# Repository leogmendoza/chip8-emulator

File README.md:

# 🍪 CHIP ATE

## 🤔 What?
CHIP ATE is a CHIP-8 Emulator implemented on both PC using SDL2 and STM32 with a custom PCB!

## 🤨 Why?
This was supposed to be my first step into console emulation, but then it became that for PCB design as well!

## Features
- **Portable Emulator Core**:  
  Implements the timers, memory, and CPU as per the [official CHIP-8 spec](http://devernay.free.fr/hacks/chip8/C8TECH10.HTM), including all 34 instructions

- **Platform Abstraction Layer**:  
  Able to run on either PC or STM32 using a platform-agnostic API layer
  
- **Custom PCB**:  
  Assembled on a STM32-based board with an OLED screen, keypad, a buzzer, and power regulation
  
- **ROM Menu**:  
  Provides seamless loading in and out of the ROM catalog

## Diagrams

### System Architecture

### Schematic

### Routing and 3D Renders

## 📸 STM32 Demos

### Demo Video (click it!)

### Tetris

### Tic-Tac-Toe

### Pong

## 📸 PC Demos

### Demo Video (click it!)

### Startup Screen

### Menu

### Opcode Test

## Resources
- [Guide to Making a CHIP-8 Emulator](https://tobiasvl.github.io/blog/write-a-chip-8-emulator/) by Tobias V. Langhoff
- [Building a CHIP-8 Emulator in C++](https://austinmorlan.com/posts/chip8_emulator/) by Austin Morlan
- [chip8stm32 Repo](https://github.com/AlfonsoJLuna/chip8stm32) by AlfonsoJLuna
- [KiCad Tutorial Playlist](https://youtube.com/playlist?list=PL3bNyZYHcRSUhUXUt51W6nKvxx2ORvUQB&si=zccgU5XXFSJnHfGM) by Shawn Hymel
- [KiCad 7 PCB Layout in 5 Steps](https://youtu.be/3FGNw28xBr0?si=mEvIMN-HYlVow5y7) by The Design Graveyard

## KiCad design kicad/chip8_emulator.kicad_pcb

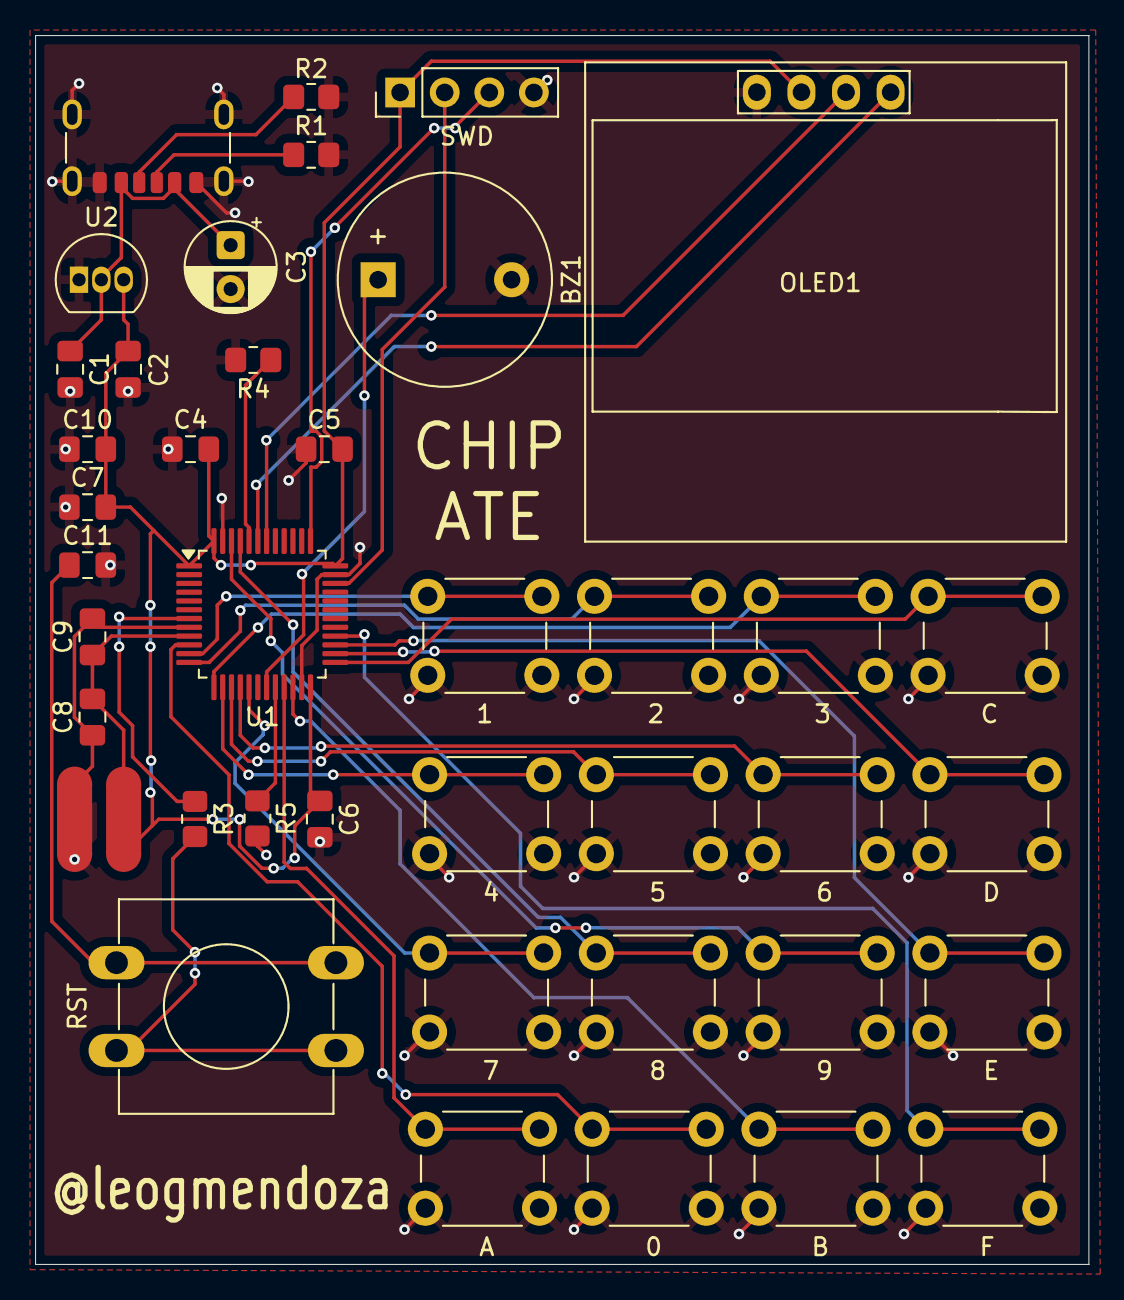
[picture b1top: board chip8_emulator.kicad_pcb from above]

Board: 2 copper layers, 60.0 x 70.0 mm, 41 parts (0 on the bottom side), 33 nets.

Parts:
BZ1: Buzzer; Buzzer_12x9.5RM7.6
C1, C2, C9: 1uF; C_0805_2012Metric_Pad1.18x1.45mm_HandSolder
C3: 10uF; CP_Radial_D5.0mm_P2.50mm
C4, C5, C6, C7, C8, C11: 100nF; C_0805_2012Metric_Pad1.18x1.45mm_HandSolder
C10: 4.7uF; C_0805_2012Metric_Pad1.18x1.45mm_HandSolder
J1: USB-C Power In; USB_C_Receptacle_GCT_USB4125-xx-x_6P_TopMnt_Horizontal
J2: SWD; PinHeader_1x04_P2.54mm_Vertical
NT1, NT2: NetTie_2; NetTie-2_SMD_Pad2.0mm
OLED1: SSD1306; 128x64OLED
R1, R2: 5.1k; R_0805_2012Metric_Pad1.20x1.40mm_HandSolder
R3, R4, R5: 10k; R_0805_2012Metric_Pad1.20x1.40mm_HandSolder
SW1: 1; SW_PUSH_6mm_H4.3mm
SW2: 2; SW_PUSH_6mm_H4.3mm
SW3: 3; SW_PUSH_6mm_H4.3mm
SW4: C; SW_PUSH_6mm_H4.3mm
SW5: 4; SW_PUSH_6mm_H4.3mm
SW6: 5; SW_PUSH_6mm_H4.3mm
SW7: 6; SW_PUSH_6mm_H4.3mm
SW8: D; SW_PUSH_6mm_H4.3mm
SW9: 7; SW_PUSH_6mm_H4.3mm
SW10: 8; SW_PUSH_6mm_H4.3mm
SW11: 9; SW_PUSH_6mm_H4.3mm
SW12: E; SW_PUSH_6mm_H4.3mm
SW13: A; SW_PUSH_6mm_H4.3mm
SW14: 0; SW_PUSH_6mm_H4.3mm
SW15: B; SW_PUSH_6mm_H4.3mm
SW16: F; SW_PUSH_6mm_H4.3mm
SW17: RST; SW_PUSH-12mm
U1: STM32F103C8Tx; LQFP-48_7x7mm_P0.5mm
U2: MCP1700x-330xxTO; TO-92_Inline

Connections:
+3V3: C2.1, C4.2, C5.2, C6.2, C7.2, C10.2, J2.1, NT1.2, OLED1.2 (VCC), U1.1 (VBAT), U1.24 (VDD), U1.36 (VDD), U1.48 (VDD), U2.3 (VO)
+5V: C1.1, C3.1, J1.A9 (VBUS), J1.B9 (VBUS), U2.2 (VI)
/BOOT0: R4.2, U1.44 (BOOT0)
/BOOT1: R5.2, U1.20 (PB2)
/BUZZER: BZ1.1 (+), U1.19 (PB1)
/I2C1_SCL: OLED1.3 (SCL), U1.42 (PB6)
/I2C1_SDA: OLED1.4 (SDA), U1.43 (PB7)
/KEY_0: SW14.1, U1.10 (PA0)
/KEY_1: SW1.1, U1.11 (PA1)
/KEY_2: SW2.1, U1.12 (PA2)
/KEY_3: SW3.1, U1.13 (PA3)
/KEY_4: SW5.1, U1.14 (PA4)
/KEY_5: SW6.1, U1.15 (PA5)
/KEY_6: SW7.1, U1.16 (PA6)
/KEY_7: SW9.1, U1.17 (PA7)
/KEY_8: SW10.1, U1.45 (PB8)
/KEY_9: SW11.1, U1.46 (PB9)
/KEY_A: SW13.1, U1.21 (PB10)
/KEY_B: SW15.1, U1.22 (PB11)
/KEY_C: SW4.1, U1.25 (PB12)
/KEY_D: SW8.1, U1.26 (PB13)
/KEY_E: SW12.1, U1.27 (PB14)
/KEY_F: SW16.1, U1.28 (PB15)
/NRST: R3.1, U1.7 (NRST)
/SWCLK: J2.3, U1.37 (PA14)
/SWDIO: J2.2, U1.34 (PA13)
/VDDA: C8.2, C9.1, NT1.1, U1.9 (VDDA)
/VSSA: C8.1, C9.2, NT2.2, U1.8 (VSSA)
GND: BZ1.2 (-), C1.2, C2.2, C3.2, C4.1, C5.1, C6.1, C7.1, C10.1, C11.1, J1.A12 (GND), J1.B12 (GND), J1.S1 (SHIELD), J2.4, NT2.1, OLED1.1 (GND), R1.2, R2.2, R4.1, R5.1, SW1.2, SW2.2, SW3.2, SW4.2, SW5.2, SW6.2, SW7.2, SW8.2, SW9.2, SW10.2, SW11.2, SW12.2, SW13.2, SW14.2, SW15.2, SW16.2, U1.23 (VSS), U1.35 (VSS), U1.47 (VSS), U2.1 (GND)
unnamed: C11.2, SW17.1
unnamed: J1.A5 (CC1), R1.1
unnamed: J1.B5 (CC2), R2.1
unnamed: R3.2, SW17.2

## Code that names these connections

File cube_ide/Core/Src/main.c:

/* USER CODE BEGIN Header */
/**
  ******************************************************************************
  * @file           : main.c
  * @brief          : Main program body
  ******************************************************************************
  * @attention
  *
  * Copyright (c) 2025 STMicroelectronics.
  * All rights reserved.
  *
  * This software is licensed under terms that can be found in the LICENSE file
  * in the root directory of this software component.
  * If no LICENSE file comes with this software, it is provided AS-IS.
  *
  ******************************************************************************
  */
/* USER CODE END Header */
/* Includes ------------------------------------------------------------------*/
#include "main.h"

/* Private includes ----------------------------------------------------------*/
/* USER CODE BEGIN Includes */
#include "chip8.h"
#include "app.h"
/* USER CODE END Includes */

/* Private typedef -----------------------------------------------------------*/
/* USER CODE BEGIN PTD */

/* USER CODE END PTD */

/* Private define ------------------------------------------------------------*/
/* USER CODE BEGIN PD */

/* USER CODE END PD */

/* Private macro -------------------------------------------------------------*/
/* USER CODE BEGIN PM */

/* USER CODE END PM */

/* Private variables ---------------------------------------------------------*/
I2C_HandleTypeDef hi2c1;

TIM_HandleTypeDef htim3;

/* USER CODE BEGIN PV */

/* USER CODE END PV */

/* Private function prototypes -----------------------------------------------*/
void SystemClock_Config(void);
static void MX_GPIO_Init(void);
static void MX_I2C1_Init(void);
static void MX_TIM3_Init(void);
/* USER CODE BEGIN PFP */

/* USER CODE END PFP */

/* Private user code ---------------------------------------------------------*/
/* USER CODE BEGIN 0 */

/* USER CODE END 0 */

/**
  * @brief  The application entry point.
  * @retval int
  */
int main(void)
{

  /* USER CODE BEGIN 1 */

  /* USER CODE END 1 */

  /* MCU Configuration--------------------------------------------------------*/

  /* Reset of all peripherals, Initializes the Flash interface and the Systick. */
  HAL_Init();

  /* USER CODE BEGIN Init */

  /* USER CODE END Init */

  /* Configure the system clock */
  SystemClock_Config();

  /* USER CODE BEGIN SysInit */

  /* USER CODE END SysInit */

  /* Initialize all configured peripherals */
  MX_GPIO_Init();
  MX_I2C1_Init();
  MX_TIM3_Init();
  /* USER CODE BEGIN 2 */

  app();

  /* USER CODE END 2 */

  /* Infinite loop */
  /* USER CODE BEGIN WHILE */
  while (1)
  {
    /* USER CODE END WHILE */

    /* USER CODE BEGIN 3 */
  }
  /* USER CODE END 3 */
}

/**
  * @brief System Clock Configuration
  * @retval None
  */
void SystemClock_Config(void)
{
  RCC_OscInitTypeDef RCC_OscInitStruct = {0};
  RCC_ClkInitTypeDef RCC_ClkInitStruct = {0};

  /** Initializes the RCC Oscillators according to the specified parameters
  * in the RCC_OscInitTypeDef structure.
  */
  RCC_OscInitStruct.OscillatorType = RCC_OSCILLATORTYPE_HSI;
  RCC_OscInitStruct.HSIState = RCC_HSI_ON;
  RCC_OscInitStruct.HSICalibrationValue = RCC_HSICALIBRATION_DEFAULT;
  RCC_OscInitStruct.PLL.PLLState = RCC_PLL_ON;
  RCC_OscInitStruct.PLL.PLLSource = RCC_PLLSOURCE_HSI_DIV2;
  RCC_OscInitStruct.PLL.PLLMUL = RCC_PLL_MUL5;
  if (HAL_RCC_OscConfig(&RCC_OscInitStruct) != HAL_OK)
  {
    Error_Handler();
  }

  /** Initializes the CPU, AHB and APB buses clocks
  */
  RCC_ClkInitStruct.ClockType = RCC_CLOCKTYPE_HCLK|RCC_CLOCKTYPE_SYSCLK
                              |RCC_CLOCKTYPE_PCLK1|RCC_CLOCKTYPE_PCLK2;
  RCC_ClkInitStruct.SYSCLKSource = RCC_SYSCLKSOURCE_PLLCLK;
  RCC_ClkInitStruct.AHBCLKDivider = RCC_SYSCLK_DIV1;
  RCC_ClkInitStruct.APB1CLKDivider = RCC_HCLK_DIV1;
  RCC_ClkInitStruct.APB2CLKDivider = RCC_HCLK_DIV1;

  if (HAL_RCC_ClockConfig(&RCC_ClkInitStruct, FLASH_LATENCY_0) != HAL_OK)
  {
    Error_Handler();
  }
}

/**
  * @brief I2C1 Initialization Function
  * @param None
  * @retval None
  */
static void MX_I2C1_Init(void)
{

  /* USER CODE BEGIN I2C1_Init 0 */

  /* USER CODE END I2C1_Init 0 */

  /* USER CODE BEGIN I2C1_Init 1 */

  /* USER CODE END I2C1_Init 1 */
  hi2c1.Instance = I2C1;
  hi2c1.Init.ClockSpeed = 400000;
  hi2c1.Init.DutyCycle = I2C_DUTYCYCLE_2;
  hi2c1.Init.OwnAddress1 = 0;
  hi2c1.Init.AddressingMode = I2C_ADDRESSINGMODE_7BIT;
  hi2c1.Init.DualAddressMode = I2C_DUALADDRESS_DISABLE;
  hi2c1.Init.OwnAddress2 = 0;
  hi2c1.Init.GeneralCallMode = I2C_GENERALCALL_DISABLE;
  hi2c1.Init.NoStretchMode = I2C_NOSTRETCH_DISABLE;
  if (HAL_I2C_Init(&hi2c1) != HAL_OK)
  {
    Error_Handler();
  }
  /* USER CODE BEGIN I2C1_Init 2 */

  /* USER CODE END I2C1_Init 2 */

}

/**
  * @brief TIM3 Initialization Function
  * @param None
  * @retval None
  */
static void MX_TIM3_Init(void)
{

  /* USER CODE BEGIN TIM3_Init 0 */

  /* USER CODE END TIM3_Init 0 */

  TIM_ClockConfigTypeDef sClockSourceConfig = {0};
  TIM_MasterConfigTypeDef sMasterConfig = {0};
  TIM_OC_InitTypeDef sConfigOC = {0};

  /* USER CODE BEGIN TIM3_Init 1 */

  /* USER CODE END TIM3_Init 1 */
  htim3.Instance = TIM3;
  htim3.Init.Prescaler = 7;
  htim3.Init.CounterMode = TIM_COUNTERMODE_UP;
  htim3.Init.Period = 499;
  htim3.Init.ClockDivision = TIM_CLOCKDIVISION_DIV1;
  htim3.Init.AutoReloadPreload = TIM_AUTORELOAD_PRELOAD_DISABLE;
  if (HAL_TIM_Base_Init(&htim3) != HAL_OK)
  {
    Error_Handler();
  }
  sClockSourceConfig.ClockSource = TIM_CLOCKSOURCE_INTERNAL;
  if (HAL_TIM_ConfigClockSource(&htim3, &sClockSourceConfig) != HAL_OK)
  {
    Error_Handler();
  }
  if (HAL_TIM_PWM_Init(&htim3) != HAL_OK)
  {
    Error_Handler();
  }
  sMasterConfig.MasterOutputTrigger = TIM_TRGO_RESET;
  sMasterConfig.MasterSlaveMode = TIM_MASTERSLAVEMODE_DISABLE;
  if (HAL_TIMEx_MasterConfigSynchronization(&htim3, &sMasterConfig) != HAL_OK)
  {
    Error_Handler();
  }
  sConfigOC.OCMode = TIM_OCMODE_PWM1;
  sConfigOC.Pulse = 0;
  sConfigOC.OCPolarity = TIM_OCPOLARITY_HIGH;
  sConfigOC.OCFastMode = TIM_OCFAST_DISABLE;
  if (HAL_TIM_PWM_ConfigChannel(&htim3, &sConfigOC, TIM_CHANNEL_4) != HAL_OK)
  {
    Error_Handler();
  }
  /* USER CODE BEGIN TIM3_Init 2 */

  /* USER CODE END TIM3_Init 2 */
  HAL_TIM_MspPostInit(&htim3);

}

/**
  * @brief GPIO Initialization Function
  * @param None
  * @retval None
  */
static void MX_GPIO_Init(void)
{
  GPIO_InitTypeDef GPIO_InitStruct = {0};
/* USER CODE BEGIN MX_GPIO_Init_1 */
/* USER CODE END MX_GPIO_Init_1 */

  /* GPIO Ports Clock Enable */
  __HAL_RCC_GPIOC_CLK_ENABLE();
  __HAL_RCC_GPIOA_CLK_ENABLE();
  __HAL_RCC_GPIOB_CLK_ENABLE();

  /*Configure GPIO pin Output Level */
  HAL_GPIO_WritePin(GPIOC, GPIO_PIN_13, GPIO_PIN_RESET);

  /*Configure GPIO pin : PC13 */
  GPIO_InitStruct.Pin = GPIO_PIN_13;
  GPIO_InitStruct.Mode = GPIO_MODE_OUTPUT_PP;
  GPIO_InitStruct.Pull = GPIO_NOPULL;
  GPIO_InitStruct.Speed = GPIO_SPEED_FREQ_LOW;
  HAL_GPIO_Init(GPIOC, &GPIO_InitStruct);

  /*Configure GPIO pins : PA0 PA1 PA2 PA3
                           PA4 PA5 PA6 PA7 */
  GPIO_InitStruct.Pin = GPIO_PIN_0|GPIO_PIN_1|GPIO_PIN_2|GPIO_PIN_3
                          |GPIO_PIN_4|GPIO_PIN_5|GPIO_PIN_6|GPIO_PIN_7;
  GPIO_InitStruct.Mode = GPIO_MODE_INPUT;
  GPIO_InitStruct.Pull = GPIO_PULLUP;
  HAL_GPIO_Init(GPIOA, &GPIO_InitStruct);

  /*Configure GPIO pins : PB10 PB11 PB12 PB13
                           PB14 PB15 PB8 PB9 */
  GPIO_InitStruct.Pin = GPIO_PIN_10|GPIO_PIN_11|GPIO_PIN_12|GPIO_PIN_13
                          |GPIO_PIN_14|GPIO_PIN_15|GPIO_PIN_8|GPIO_PIN_9;
  GPIO_InitStruct.Mode = GPIO_MODE_INPUT;
  GPIO_InitStruct.Pull = GPIO_PULLUP;
  HAL_GPIO_Init(GPIOB, &GPIO_InitStruct);

/* USER CODE BEGIN MX_GPIO_Init_2 */
/* USER CODE END MX_GPIO_Init_2 */
}

/* USER CODE BEGIN 4 */

/* USER CODE END 4 */

/**
  * @brief  This function is executed in case of error occurrence.
  * @retval None
  */
void Error_Handler(void)
{
  /* USER CODE BEGIN Error_Handler_Debug */
  /* User can add his own implementation to report the HAL error return state */
  __disable_irq();
  while (1)
  {
  }
  /* USER CODE END Error_Handler_Debug */
}

#ifdef  USE_FULL_ASSERT
/**
  * @brief  Reports the name of the source file and the source line number
  *         where the assert_param error has occurred.
  * @param  file: pointer to the source file name
  * @param  line: assert_param error line source number
  * @retval None
  */
void assert_failed(uint8_t *file, uint32_t line)
{
  /* USER CODE BEGIN 6 */
  /* User can add his own implementation to report the file name and line number,
     ex: printf("Wrong parameters value: file %s on line %d\r\n", file, line) */
  /* USER CODE END 6 */
}
#endif /* USE_FULL_ASSERT */

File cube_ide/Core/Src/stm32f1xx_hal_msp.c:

/* USER CODE BEGIN Header */
/**
  ******************************************************************************
  * @file         stm32f1xx_hal_msp.c
  * @brief        This file provides code for the MSP Initialization
  *               and de-Initialization codes.
  ******************************************************************************
  * @attention
  *
  * Copyright (c) 2025 STMicroelectronics.
  * All rights reserved.
  *
  * This software is licensed under terms that can be found in the LICENSE file
  * in the root directory of this software component.
  * If no LICENSE file comes with this software, it is provided AS-IS.
  *
  ******************************************************************************
  */
/* USER CODE END Header */

/* Includes ------------------------------------------------------------------*/
#include "main.h"
/* USER CODE BEGIN Includes */

/* USER CODE END Includes */

/* Private typedef -----------------------------------------------------------*/
/* USER CODE BEGIN TD */

/* USER CODE END TD */

/* Private define ------------------------------------------------------------*/
/* USER CODE BEGIN Define */

/* USER CODE END Define */

/* Private macro -------------------------------------------------------------*/
/* USER CODE BEGIN Macro */

/* USER CODE END Macro */

/* Private variables ---------------------------------------------------------*/
/* USER CODE BEGIN PV */

/* USER CODE END PV */

/* Private function prototypes -----------------------------------------------*/
/* USER CODE BEGIN PFP */

/* USER CODE END PFP */

/* External functions --------------------------------------------------------*/
/* USER CODE BEGIN ExternalFunctions */

/* USER CODE END ExternalFunctions */

/* USER CODE BEGIN 0 */

/* USER CODE END 0 */

void HAL_TIM_MspPostInit(TIM_HandleTypeDef *htim);
                    /**
  * Initializes the Global MSP.
  */
void HAL_MspInit(void)
{

  /* USER CODE BEGIN MspInit 0 */

  /* USER CODE END MspInit 0 */

  __HAL_RCC_AFIO_CLK_ENABLE();
  __HAL_RCC_PWR_CLK_ENABLE();

  /* System interrupt init*/

  /** NOJTAG: JTAG-DP Disabled and SW-DP Enabled
  */
  __HAL_AFIO_REMAP_SWJ_NOJTAG();

  /* USER CODE BEGIN MspInit 1 */

  /* USER CODE END MspInit 1 */
}

/**
* @brief I2C MSP Initialization
* This function configures the hardware resources used in this example
* @param hi2c: I2C handle pointer
* @retval None
*/
void HAL_I2C_MspInit(I2C_HandleTypeDef* hi2c)
{
  GPIO_InitTypeDef GPIO_InitStruct = {0};
  if(hi2c->Instance==I2C1)
  {
  /* USER CODE BEGIN I2C1_MspInit 0 */

  /* USER CODE END I2C1_MspInit 0 */

    __HAL_RCC_GPIOB_CLK_ENABLE();
    /**I2C1 GPIO Configuration
    PB6     ------> I2C1_SCL
    PB7     ------> I2C1_SDA
    */
    GPIO_InitStruct.Pin = GPIO_PIN_6|GPIO_PIN_7;
    GPIO_InitStruct.Mode = GPIO_MODE_AF_OD;
    GPIO_InitStruct.Speed = GPIO_SPEED_FREQ_HIGH;
    HAL_GPIO_Init(GPIOB, &GPIO_InitStruct);

    /* Peripheral clock enable */
    __HAL_RCC_I2C1_CLK_ENABLE();
  /* USER CODE BEGIN I2C1_MspInit 1 */

  /* USER CODE END I2C1_MspInit 1 */

  }

}

/**
* @brief I2C MSP De-Initialization
* This function freeze the hardware resources used in this example
* @param hi2c: I2C handle pointer
* @retval None
*/
void HAL_I2C_MspDeInit(I2C_HandleTypeDef* hi2c)
{
  if(hi2c->Instance==I2C1)
  {
  /* USER CODE BEGIN I2C1_MspDeInit 0 */

  /* USER CODE END I2C1_MspDeInit 0 */
    /* Peripheral clock disable */
    __HAL_RCC_I2C1_CLK_DISABLE();

    /**I2C1 GPIO Configuration
    PB6     ------> I2C1_SCL
    PB7     ------> I2C1_SDA
    */
    HAL_GPIO_DeInit(GPIOB, GPIO_PIN_6);

    HAL_GPIO_DeInit(GPIOB, GPIO_PIN_7);

  /* USER CODE BEGIN I2C1_MspDeInit 1 */

  /* USER CODE END I2C1_MspDeInit 1 */
  }

}

/**
* @brief TIM_Base MSP Initialization
* This function configures the hardware resources used in this example
* @param htim_base: TIM_Base handle pointer
* @retval None
*/
void HAL_TIM_Base_MspInit(TIM_HandleTypeDef* htim_base)
{
  if(htim_base->Instance==TIM3)
  {
  /* USER CODE BEGIN TIM3_MspInit 0 */

  /* USER CODE END TIM3_MspInit 0 */
    /* Peripheral clock enable */
    __HAL_RCC_TIM3_CLK_ENABLE();
  /* USER CODE BEGIN TIM3_MspInit 1 */

  /* USER CODE END TIM3_MspInit 1 */

  }

}

void HAL_TIM_MspPostInit(TIM_HandleTypeDef* htim)
{
  GPIO_InitTypeDef GPIO_InitStruct = {0};
  if(htim->Instance==TIM3)
  {
  /* USER CODE BEGIN TIM3_MspPostInit 0 */

  /* USER CODE END TIM3_MspPostInit 0 */

    __HAL_RCC_GPIOB_CLK_ENABLE();
    /**TIM3 GPIO Configuration
    PB1     ------> TIM3_CH4
    */
    GPIO_InitStruct.Pin = GPIO_PIN_1;
    GPIO_InitStruct.Mode = GPIO_MODE_AF_PP;
    GPIO_InitStruct.Speed = GPIO_SPEED_FREQ_LOW;
    HAL_GPIO_Init(GPIOB, &GPIO_InitStruct);

  /* USER CODE BEGIN TIM3_MspPostInit 1 */

  /* USER CODE END TIM3_MspPostInit 1 */
  }

}
/**
* @brief TIM_Base MSP De-Initialization
* This function freeze the hardware resources used in this example
* @param htim_base: TIM_Base handle pointer
* @retval None
*/
void HAL_TIM_Base_MspDeInit(TIM_HandleTypeDef* htim_base)
{
  if(htim_base->Instance==TIM3)
  {
  /* USER CODE BEGIN TIM3_MspDeInit 0 */

  /* USER CODE END TIM3_MspDeInit 0 */
    /* Peripheral clock disable */
    __HAL_RCC_TIM3_CLK_DISABLE();
  /* USER CODE BEGIN TIM3_MspDeInit 1 */

  /* USER CODE END TIM3_MspDeInit 1 */
  }

}

/* USER CODE BEGIN 1 */

/* USER CODE END 1 */

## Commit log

2025-07-08 Starting my CHIP-8 project finallaayyyyyy!
2025-07-08 Set up CMake
2025-07-13 Structure (pun intended) the Chip8 struct!
2025-07-24 Start defining memory and ROM
2025-07-24 Set up load_rom implementation!
2025-08-20 Write ROM loader
2025-08-20 Abstract fileio away from platform-independent rom.c
2025-08-20 Create rom_loader interface for separating platforms
2025-08-20 Use platform independent mem helpers
2025-08-20 Add some resets in chip8 init
2025-08-20 Create table for func ptrs for each fetching instructions
2025-08-21 Implemented almosttt all needed instructions for first test
2025-08-23 Finish WOO
2025-08-23 Resolve Cmake issues and prep main
2025-08-24 Implement a lil more instructions for IBM logo
2025-08-24 DISPLAYED THE IBM LOGO WOOOOO
2025-08-24 Implement instruction skip operations
2025-08-24 Implement rand_byte algo, other table dispatch funcs, rest of skips
2025-08-24 Set up table F instructions
2025-08-25 FINISH ALL INSTRUCTIONS AYYEEE
2025-08-25 Fix major bugs of instructions
2025-08-25 Finally... my test ROMs are working at last and it was all due to a copypasta error from my dispatch functions CRYINGGDSFKJNHJKDSHFSDF
2025-08-25 Implement input. Good nightgit add .
2025-08-25 WOOOO BABY TESTED TETRIS, SPACE INVADERS, AND PONG SUCCESSFULLY AFTER SOOOO MUCH DEBUGGING
2025-08-25 Fix minor bugs with drawing and mem safety
2025-08-25 Implement SDL sound
2025-08-26 Try out many games!
2025-08-26 Clean up config params
2025-08-27 Setup menu files
2025-08-28 Tested menu screen B)
2025-08-28 Finally scaled down font.... manually
2025-08-29 tested display, uncommented erthing else, did not work due to unsoldered board
2025-08-29 Soldered MCU header pins and implemented input >:D
2025-08-30 Implement sound!
2025-08-30 WOOOOO ROM loading worksgit add .!
2025-09-26 Final draft to MCU
2025-09-26 Add STM32CubeIDE files
2025-09-26 Add KiCad files
2025-09-26 Add assets
2025-09-26 Added drawio
2025-10-15 Rename space_invaders.png to space_invaders_pc.png
2025-10-15 Add last product photos
